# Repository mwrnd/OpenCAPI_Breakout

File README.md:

# OpenCAPI Breakout

[OpenCAPI](https://files.openpower.foundation/s/xSQPe6ypoakKQdq/download/25Gbps-spec-20171108.pdf) to [U.FL/UMCC Connector](https://en.wikipedia.org/wiki/Hirose_U.FL) breakout.

I have [successfully tested](https://github.com/mwrnd/innova2_experiments/tree/main/xdma_opencapi) the board using [3M 8ES8-1DF21](https://www.trustedparts.com/en/search/8ES8-1DF21-0.75)([Datasheet](https://multimedia.3m.com/mws/media/1398233O/3m-slimline-twin-ax-assembly-sff-8654-x8-30awg-78-5100-2665-8.pdf)) and
 [SlimSAS SFF-8654 8i 85-Ohm](https://www.sfpcables.com/24g-internal-slimsas-sff-8654-to-sff-8654-8i-cable-straight-to-90-degree-left-angle-8x-12-sas-4-0-85-ohm-0-5-1-meter)([Archived](https://web.archive.org/web/20210121175017/https://www.sfpcables.com/24g-internal-slimsas-sff-8654-to-sff-8654-8i-cable-straight-to-90-degree-left-angle-8x-12-sas-4-0-85-ohm-0-5-1-meter)) cables. The 3M Cable has better performance.

No consideration was given to pinout compatibility with the [SlimSAS SFF-8654 Standard](https://members.snia.org/document/dl/26744).

The [Open Coherant Accelerator Processor Interface](https://opencapi.org/wp-content/uploads/2022/07/OpenCAPI-Overview.pdf) (OpenCAPI) [was a standard](https://opencapi.org/2022/08/09/cxl-consortium-and-opencapi-consortium-sign-letter-of-intent-to-transfer-opencapi-specifications-to-cxl/) that had FPGA-based [Advanced Accelerated Cable](https://files.openpower.foundation/s/xSQPe6ypoakKQdq/download/25Gbps-spec-20171108.pdf) (AAC) [Add-In cards](https://opencapi.org/wp-content/uploads/2018/12/OpenCAPI-Tech-SC18-Exhibitor-Forum.pdf) such as [ADM-PCIE-9H3](https://www.alpha-data.com/product/adm-pcie-9h3/), [ADM-PCIE-9H7](https://www.alpha-data.com/alpha-data-release-adm-pcie-9h7-data-center-board-with-xilinx-virtex-ultrascale-hbm-fpga/), [ADM-PCIE-9V3](https://www.alpha-data.com/product/adm-pcie-9v3/), [ADM-PCIE-9V5](https://www.alpha-data.com/product/adm-pcie-9v5/), [BittWare XUPSVH](https://static5.arrow.com/pdfs/2018/10/26/23/28/4/364872/btwr_/manual/ds-xupsvh.pdf), [BittWare XUP-VV4](https://www.bittware.com/fpga/xup-vv4/), [BittWare XUP-VVH](https://www.bittware.com/fpga/xup-vvh/), and [Nvidia Innova-2 Flex](https://www.nvidia.com/en-us/networking/ethernet/innova-2-flex/).

Related Projects: [PCIe_x8_Breakout](https://github.com/mwrnd/PCIe_x8_Breakout), [OpenCAPI-to-PCIe](https://github.com/mwrnd/OpenCAPI-to-PCIe), [OpenCAPI-to-PCIe_x4_Host_and_Endpoint](https://github.com/mwrnd/OpenCAPI-to-PCIe_x4_Host_and_Endpoint), [QSFP_Breakout](https://github.com/mwrnd/QSFP_Breakout), [HDMI_Breakout](https://github.com/mwrnd/HDMI_Breakout), [SFP_Plug_Breakout](https://github.com/mwrnd/SFP_Plug_Breakout)

# Testing and Use Example

This board can be used along with a [PCIe_x8_Breakout](https://github.com/mwrnd/PCIe_x8_Breakout) board to test [OpenCAPI-to-PCIe](https://github.com/mwrnd/innova2_experiments/tree/main/xdma_opencapi) on the [Innova-2 SmartNIC](https://www.nvidia.com/en-us/networking/ethernet/innova-2-flex/). PCIe 3.0 x4 at 8.0GT/s works. Standard [0.1" M-F Jumpers](https://www.digikey.com/en/products/detail/adafruit-industries-llc/1954/6827087) are used for the PCIe Reset Signal (*nPERST*) and its GND.

With cables shorter than 100mm~=4" the [adapters work](https://github.com/mwrnd/innova2_experiments/tree/main/xdma_opencapi). The [RX U.FL-to-U.FL cables](https://www.digikey.com/en/products/detail/te-connectivity-amp-connectors/2118651-6/11205742) are all the same length as each other and likewise all [TX cables](https://www.digikey.com/en/products/detail/te-connectivity-amp-connectors/2015698-2/1249186) are the same length but RX and TX are different lengths as that is what I had available. RX on the PCIe board connects to RX on the OpenCAPI board as it uses the OpenCAPI Host pinout.

PCIe x4 In-system:

However, using 250mm IPEX cables the adapters fail for PCIe x8:

PCIe x8 In-system:

# First Revision

Main difference between the First and Second Revisions is their silkscreen labelling. Both are based on the pinout from the [ADM-PCIE-9V5 User Manual (Pg15-19of38)](https://www.alpha-data.com/xml/user_manuals/adm-pcie-9v5%20user%20manual_v1_4.pdf).

The First Revision uses the OpenCAPI **Host** pinout which is the row A-to-B/B-to-A swapped version of the **Carrier** pinout that is used on OpenCAPI AAC Add-In cards. When used with a [PCIe_x8_Breakout](https://github.com/mwrnd/PCIe_x8_Breakout) **Rx** signals connect to **Rx** and **Tx** to **Tx**.

Labels are relative to the Host. Host RX is Carrier TX and vice versa so the **Rx** pins on this board have transmitter signals from the Add-in card on them. **Tx** pins connect to the Add-in card's receiver signals.

## PCB Layout

## Schematic

# Second Revision

The Second Revision changes the silkscreen to label the U.FL connectors with the signal that is on them. **Tx** pins connect to the Add-In card's transmitter pins and **Rx** signals connect to receiver pins.

The board also annotates the corresponding GTY channels when connected to an MNV303212A Rev.A2 board. The MNV303212A's [swapped differential pairs](https://github.com/mwrnd/innova2_flex_xcku15p_notes/tree/main/hardware_notes#testing-mnv303212a-adlt-opencapi-connections) are also annotated.

When used with a [PCIe_x8_Breakout](https://github.com/mwrnd/PCIe_x8_Breakout) **Rx** signals connect to PCIe **Tx** and **Tx** to **Rx**.

## PCB Layout

## Schematic

# Design Notes

All differential pairs are length-matched to within 1mm both inter-pair and intra-pair.

The board requires a [U10A474200T](https://www.digikey.com/en/products/detail/amphenol-cs-commercial-products/U10A474200T/14632855)/[U10A474240T](https://www.digikey.com/en/products/detail/amphenol-cs-commercial-products/U10A474240T/17066204) SlimSAS 74-Pin Receptacle, up to 34 [U.FL/UMCC Surface Mount Receptacles](https://www.digikey.com/en/products/detail/te-connectivity-amp-connectors/2337019-1/9974052), and a 5-Pin 2.54mm [Header](https://www.digikey.com/en/products/detail/sullins-connector-solutions/PREC005SAAN-RC/2774849) or [Socket](https://www.digikey.com/en/products/detail/sullins-connector-solutions/PPPC051LFBN-RC/810177).

## PCB Layer Stackup

4-Layer PCB stackup taken from [JLCPCB](https://jlcpcb.com/capabilities/pcb-capabilities).

Differential Impedance parameters were calculated using the [DigiKey Online Calculator](https://www.digikey.com/en/resources/conversion-calculators/conversion-calculator-pcb-trace-impedance).

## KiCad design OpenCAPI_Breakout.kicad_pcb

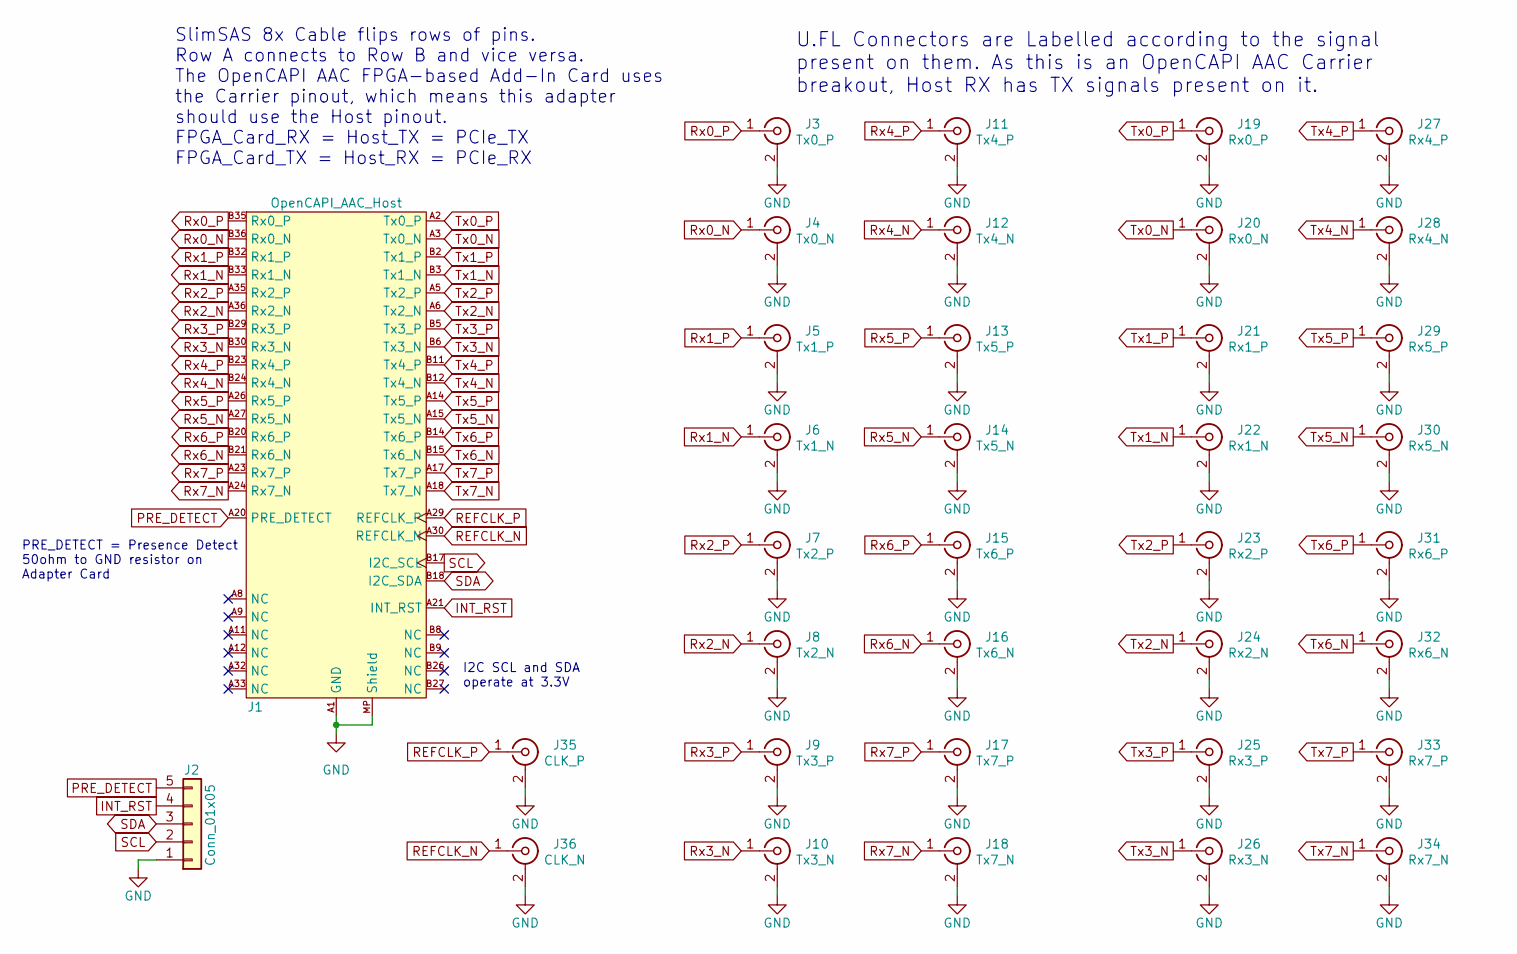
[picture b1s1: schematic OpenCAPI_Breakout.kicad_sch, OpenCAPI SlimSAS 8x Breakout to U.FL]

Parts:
J1: OpenCAPI_AAC_Host; SlimSAS_8x_RA_U10-A474
J2: Conn_01x05; PinSocket_1x05_P2.54mm_Vertical
J3: Tx0_P; U.FL_Hirose_w_Label
J4: Tx0_N; U.FL_Hirose_w_Label
J5: Tx1_P; U.FL_Hirose_w_Label
J6: Tx1_N; U.FL_Hirose_w_Label
J7: Tx2_P; U.FL_Hirose_w_Label
J8: Tx2_N; U.FL_Hirose_w_Label
J9: Tx3_P; U.FL_Hirose_w_Label
J10: Tx3_N; U.FL_Hirose_w_Label
J11: Tx4_P; U.FL_Hirose_w_Label
J12: Tx4_N; U.FL_Hirose_w_Label
J13: Tx5_P; U.FL_Hirose_w_Label
J14: Tx5_N; U.FL_Hirose_w_Label
J15: Tx6_P; U.FL_Hirose_w_Label
J16: Tx6_N; U.FL_Hirose_w_Label
J17: Tx7_P; U.FL_Hirose_w_Label
J18: Tx7_N; U.FL_Hirose_w_Label
J19: Rx0_P; U.FL_Hirose_w_Label
J20: Rx0_N; U.FL_Hirose_w_Label
J21: Rx1_P; U.FL_Hirose_w_Label
J22: Rx1_N; U.FL_Hirose_w_Label
J23: Rx2_P; U.FL_Hirose_w_Label
J24: Rx2_N; U.FL_Hirose_w_Label
J25: Rx3_P; U.FL_Hirose_w_Label
J26: Rx3_N; U.FL_Hirose_w_Label
J27: Rx4_P; U.FL_Hirose_w_Label
J28: Rx4_N; U.FL_Hirose_w_Label
J29: Rx5_P; U.FL_Hirose_w_Label
J30: Rx5_N; U.FL_Hirose_w_Label
J31: Rx6_P; U.FL_Hirose_w_Label
J32: Rx6_N; U.FL_Hirose_w_Label
J33: Rx7_P; U.FL_Hirose_w_Label
J34: Rx7_N; U.FL_Hirose_w_Label
J35: CLK_P; U.FL_Hirose_w_Label
J36: CLK_N; U.FL_Hirose_w_Label

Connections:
GND: J1.A1 (GND), J1.A4 (GND), J1.A7 (GND), J1.A10 (GND), J1.A13 (GND), J1.A16 (GND), J1.A19 (GND), J1.A22 (GND), J1.A25 (GND), J1.A28 (GND), J1.A31 (GND), J1.A34 (GND), J1.A37 (GND), J1.B1 (GND), J1.B4 (GND), J1.B7 (GND), J1.B10 (GND), J1.B13 (GND), J1.B16 (GND), J1.B19 (GND), J1.B22 (GND), J1.B25 (GND), J1.B28 (GND), J1.B31 (GND), J1.B34 (GND), J1.B37 (GND), J1.MP (Shield), J2.1, J3.2 (Ext), J4.2 (Ext), J5.2 (Ext), J6.2 (Ext), J7.2 (Ext), J8.2 (Ext), J9.2 (Ext), J10.2 (Ext), J11.2 (Ext), J12.2 (Ext), J13.2 (Ext), J14.2 (Ext), J15.2 (Ext), J16.2 (Ext), J17.2 (Ext), J18.2 (Ext), J19.2 (Ext), J20.2 (Ext), J21.2 (Ext), J22.2 (Ext), J23.2 (Ext), J24.2 (Ext), J25.2 (Ext), J26.2 (Ext), J27.2 (Ext), J28.2 (Ext), J29.2 (Ext), J30.2 (Ext), J31.2 (Ext), J32.2 (Ext), J33.2 (Ext), J34.2 (Ext), J35.2 (Ext), J36.2 (Ext)
INT_RST: J1.A21 (INT_RST), J2.4
PRE_DETECT: J1.A20 (PRE_DETECT), J2.5
REFCLK_N: J1.A30 (REFCLK_N), J36.1 (In)
REFCLK_P: J1.A29 (REFCLK_P), J35.1 (In)
Rx0_N: J1.B36 (Rx0_N), J4.1 (In)
Rx0_P: J1.B35 (Rx0_P), J3.1 (In)
Rx1_N: J1.B33 (Rx1_N), J6.1 (In)
Rx1_P: J1.B32 (Rx1_P), J5.1 (In)
Rx2_N: J1.A36 (Rx2_N), J8.1 (In)
Rx2_P: J1.A35 (Rx2_P), J7.1 (In)
Rx3_N: J1.B30 (Rx3_N), J10.1 (In)
Rx3_P: J1.B29 (Rx3_P), J9.1 (In)
Rx4_N: J1.B24 (Rx4_N), J12.1 (In)
Rx4_P: J1.B23 (Rx4_P), J11.1 (In)
Rx5_N: J1.A27 (Rx5_N), J14.1 (In)
Rx5_P: J1.A26 (Rx5_P), J13.1 (In)
Rx6_N: J1.B21 (Rx6_N), J16.1 (In)
Rx6_P: J1.B20 (Rx6_P), J15.1 (In)
Rx7_N: J1.A24 (Rx7_N), J18.1 (In)
Rx7_P: J1.A23 (Rx7_P), J17.1 (In)
SCL: J1.B17 (I2C_SCL), J2.2
SDA: J1.B18 (I2C_SDA), J2.3
Tx0_N: J1.A3 (Tx0_N), J20.1 (In)
Tx0_P: J1.A2 (Tx0_P), J19.1 (In)
Tx1_N: J1.B3 (Tx1_N), J22.1 (In)
Tx1_P: J1.B2 (Tx1_P), J21.1 (In)
Tx2_N: J1.A6 (Tx2_N), J24.1 (In)
Tx2_P: J1.A5 (Tx2_P), J23.1 (In)
Tx3_N: J1.B6 (Tx3_N), J26.1 (In)
Tx3_P: J1.B5 (Tx3_P), J25.1 (In)
Tx4_N: J1.B12 (Tx4_N), J28.1 (In)
Tx4_P: J1.B11 (Tx4_P), J27.1 (In)
Tx5_N: J1.A15 (Tx5_N), J30.1 (In)
Tx5_P: J1.A14 (Tx5_P), J29.1 (In)
Tx6_N: J1.B15 (Tx6_N), J32.1 (In)
Tx6_P: J1.B14 (Tx6_P), J31.1 (In)
Tx7_N: J1.A18 (Tx7_N), J34.1 (In)
Tx7_P: J1.A17 (Tx7_P), J33.1 (In)

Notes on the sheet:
I2C SCL and SDA operate at 3.3V
SlimSAS 8x Cable flips rows of pins. Row A connects to Row B and vice versa. The OpenCAPI AAC FPGA-based Add-In Card uses the Carrier pinout, which means this adapter should use the Host pinout. FPGA_Card_RX = Host_TX = PCIe_TX FPGA_Card_TX = Host_RX = PCIe_RX
U.FL Connectors are Labelled according to the signal present on them. As this is an OpenCAPI AAC Carrier breakout, Host RX has TX signals present on it.
PRE_DETECT = Presence Detect 50ohm to GND resistor on Adapter Card

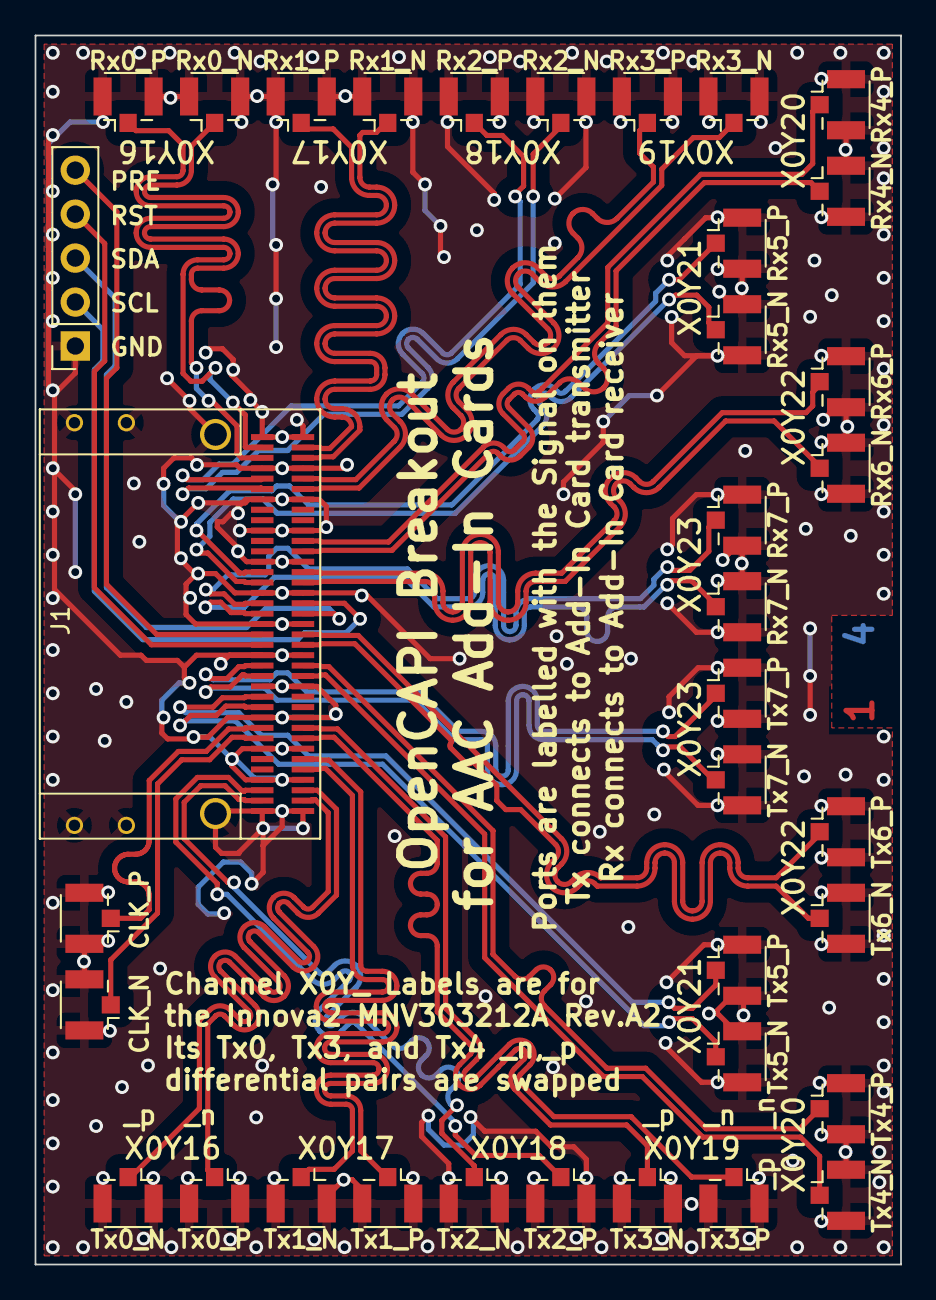
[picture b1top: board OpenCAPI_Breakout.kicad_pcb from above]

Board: 4 copper layers, 50.0 x 71.0 mm, 36 parts (0 on the bottom side), 39 nets.

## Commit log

2023-06-10 First Revision
2023-11-12 Completed Rename
2023-11-28 PCIe x8 Update
2024-03-05 Second Revision
